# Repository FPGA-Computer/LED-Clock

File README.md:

This is an accurate 6 digitals clock (HH.MM.SS) for the STM8S003.

Details: https://hw-by-design.blogspot.com/2019/11/stm8-led-clock-part-1.html

The RTC is implemented in firmware. It uses a 24-bit numerically-controlled 
oscillator (NCO) in formware for very fine accuracy adjustment.

Mine has been calibrated to within +/- 1 sec/month 
(room temperature is regulated by heaters.)

Common cathode/ 

efficient new 7 seg display with common cathode ~20mA

Common anode display/ 

old Alarm clock with recycled vintage large display from cable converter + 2 small displays. ~50mA
PNP anode drivers is needed.  Smaller display is more efficient, so I adjust their duty cycle in firmware.

Under those 2 directories:

Hardware/ - Eagle CAD schematic, PCB

Firmware/ - STM8S003 firmware source code

Firmware written by me are licensed under GPL 3.0.
It can be compiled using the free STM8 Cosmic C compiler.
Additional incorporated code are under their own licenses.

Hardware is licensed under CC BY-4.0

https://creativecommons.org/licenses/by/4.0/

History:

Initial release:
- bare minimal functionality, clock trim value is hard coded.

0.1 release
- added calendar

0.2 release
- added North America Daylight Saving Time (DST) + code clean up

0.3 release
- code cleanup
- added AC alarm clock using common anode display. Sorry messy wiring only, so no PCB

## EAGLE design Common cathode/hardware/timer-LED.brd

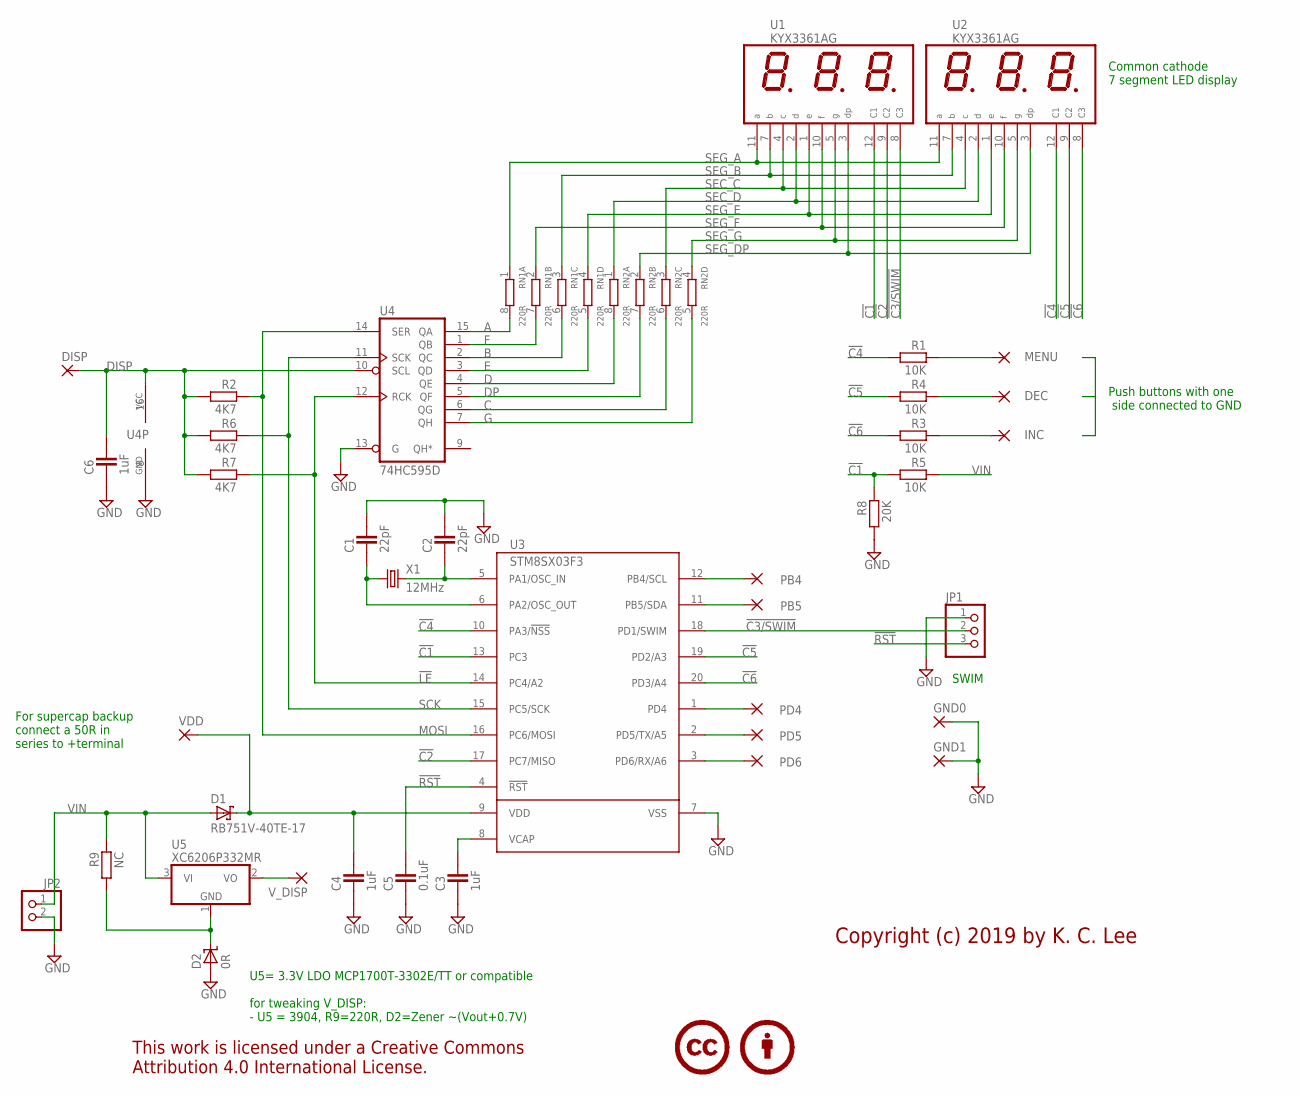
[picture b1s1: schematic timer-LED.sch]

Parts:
C1, C2: 22pF; CAPC1608X92N
C3, C4: 1uF; CAPC1608X92N
C5: 0.1uF; CAPC1608X92N
C6: 1uF; CAP2012X70N
D1: RB751V-40TE-17; SOD2514X100N
D2: 0R; SOD2514X100N
DEC: SMD2; SMD1,27-2,54
DISP: SMD2; SMD1,27-2,54
GND0, GND1: SMD2; SMD1,27-2,54
INC: SMD2; SMD1,27-2,54
JP1: PINHD-1X3; 1X03
JP2: PINHD-1X2_2.54; 1X02
LICENSE1: CC-BY75%; CC-BY-75
MENU: SMD2; SMD1,27-2,54
PB4, PB5: SMD2; SMD1,27-2,54
PD4, PD5, PD6: SMD2; SMD1,27-2,54
R1, R5: 10K; RESC1608X55N
R2, R6, R7: 4K7; RESC1608X55N
R3, R4: 10K; RESC2012X70N
R8: 20K; RESC1608X55N
R9: NC; RESC1608X55N
RN1, RN2: 220R; CAT16
U1, U2: KYX3361AG; KYX3361
U3: STM8SX03F3; TSSOP20
U4: 74HC595D; SO16
U5: XC6206P332MR; SOT95P280X135-3N
VDD: SMD2; SMD1,27-2,54
V_DISP: SMD2; SMD1,27-2,54
X1: 12MHz; HC49U-V

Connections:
!C1: R5.2, R8.1, U1.12 (C1), U3.13 (PC3)
!C2: U1.9 (C2), U3.17 (PC7/MISO)
!C3/SWIM: JP1.2, U1.8 (C3), U3.18 (PD1/SWIM)
!C4: R1.2, U2.12 (C1), U3.10 (PA3/!NSS)
!C5: R4.2, U2.9 (C2), U3.19 (PD2/A3)
!C6: R3.2, U2.8 (C3), U3.20 (PD3/A4)
!LE: R7.1, U3.14 (PC4/A2), U4.12 (RCK)
!RST: C5.2, JP1.3, U3.4 (!RST)
A: RN1.8 (2), U4.15 (QA)
B: RN1.6 (2), U4.2 (QC)
C: RN2.6 (2), U4.6 (QG)
D: RN2.8 (2), U4.4 (QE)
DISP: C6.2, DISP.1, R2.2, R6.2, R7.2, U4.10 (SCL), U4.16 (VCC)
DP: RN2.7 (2), U4.5 (QF)
E: RN1.5 (2), U4.3 (QD)
F: RN1.7 (2), U4.1 (QB)
G: RN2.5 (2), U4.7 (QH)
GND: C1.2, C2.2, C3.1, C4.1, C5.1, C6.1, D2.A, GND0.1, GND1.1, JP1.1, JP2.2, R8.2, U3.7 (VSS), U4.8 (GND), U4.13 (G)
MOSI: R2.1, U3.16 (PC6/MOSI), U4.14 (SER)
unnamed: DEC.1, R4.1
unnamed: PB4.1, U3.12 (PB4/SCL)
unnamed: PB5.1, U3.11 (PB5/SDA)
unnamed: PD5.1, U3.2 (PD5/TX/A5)
unnamed: PD6.1, U3.3 (PD6/RX/A6)
unnamed: PD4.1, U3.1 (PD4)
unnamed: INC.1, R3.1
unnamed: U5.2 (VO), V_DISP.1
unnamed: C1.1, U3.6 (PA2/OSC_OUT), X1.1
unnamed: D2.K, R9.2, U5.1 (GND)
unnamed: C2.1, U3.5 (PA1/OSC_IN), X1.2
unnamed: C3.2, U3.8 (VCAP)
unnamed: MENU.1, R1.1
SCK: R6.1, U3.15 (PC5/SCK), U4.11 (SCK)
SEC_C: RN2.3 (1), U1.4 (C), U2.4 (C)
SEC_D: RN2.1, U1.2 (D), U2.2 (D)
SEG_A: RN1.1, U1.11 (A), U2.11 (A)
SEG_B: RN1.3 (1), U1.7 (B), U2.7 (B)
SEG_DP: RN2.2 (1), U1.3 (DP), U2.3 (DP)
SEG_E: RN1.4 (1), U1.1 (E), U2.1 (E)
SEG_F: RN1.2 (1), U1.10 (F), U2.10 (F)
SEG_G: RN2.4 (1), U1.5 (G), U2.5 (G)
VDD: C4.2, D1.K, U3.9 (VDD), VDD.1
VIN: D1.A, JP2.1, R5.1, R9.1, U5.3 (VI)

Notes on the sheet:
SWIM
U5= 3.3V LDO MCP1700T-3302E/TT or compatible for tweaking V_DISP: - U5 = 3904, R9=220R, D2=Zener ~(Vout+0.7V)
Copyright (c) 2019 by K. C. Lee
Push buttons with one side connected to GND
For supercap backup connect a 50R in series to +terminal
Common cathode 7 segment LED display

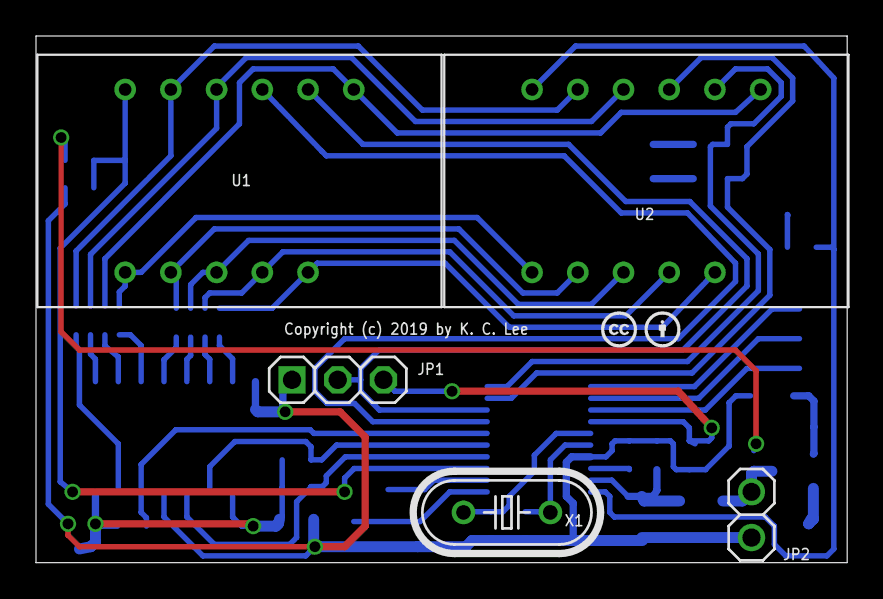
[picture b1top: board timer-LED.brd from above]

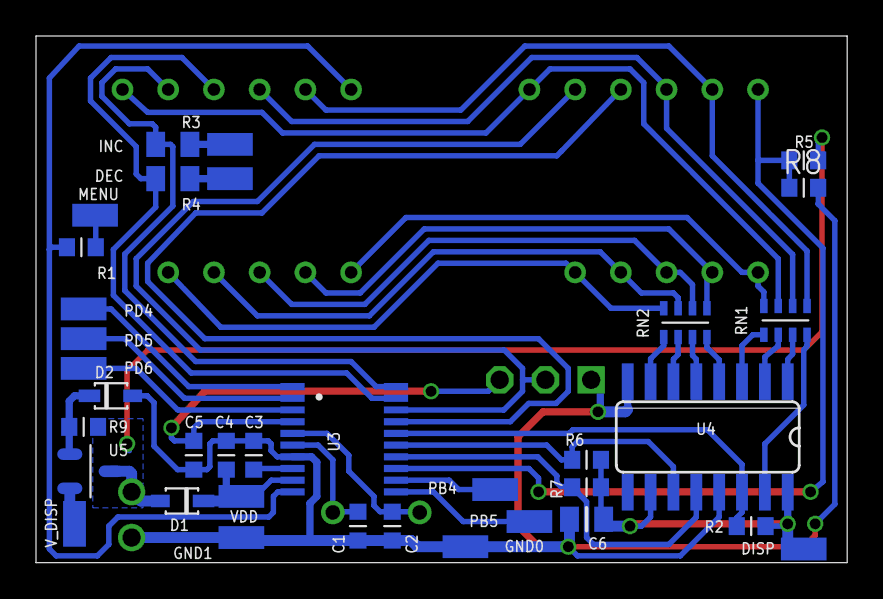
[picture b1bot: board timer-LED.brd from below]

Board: 2 copper layers, 45.1 x 29.3 mm, 41 parts (35 on the bottom side), 43 nets.

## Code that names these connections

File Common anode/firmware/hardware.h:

/*
 * hardware.h
 *
 * Created: October 31, 2019, 12:33:01 PM
 *  Author: K. C. Lee
 * Copyright (c) 2019 by K. C. Lee
 
 This program is free software: you can redistribute it and/or modify
 it under the terms of the GNU General Public License as published by
 the Free Software Foundation, either version 3 of the License, or
 (at your option) any later version.

 This program is distributed in the hope that it will be useful,
 but WITHOUT ANY WARRANTY; without even the implied warranty of
 MERCHANTABILITY or FITNESS FOR A PARTICULAR PURPOSE.  See the
 GNU General Public License for more details.

 You should have received a copy of the GNU General Public License
 along with this program.

 If not, see http://www.gnu.org/licenses/gpl-3.0.en.html 
 */ 

#ifndef HARDWARE_H_
#define HARDWARE_H_

#ifndef __CSMC__
#define __CSMC__
#endif
#define STM8S003

#include "stm8s.h"
#include <stdio.h>

// STM8S003F3P6
enum _PA { PA1=0x02, PA2=0x04, PA3=0x08 };
enum _PB { PB4=0x10, PB5=0x20 };
enum _PC { PC3=0x08, PC4=0x10, PC5=0x20, PC6=0x40, PC7=0x80 };
enum _PD { PD1=0x02, PD2=0x04, PD3=0x08, PD4=0x10, PD5=0x20, PD6=0x40 };

enum _7SEG_ENCODE
{
	SEG_A=0x01,SEG_F=0x02,SEG_B=0x04,SEG_E=0x08,
	SEG_D=0x10,SEG_DP=0x20,SEG_C=0x40,SEG_G=0x80
};

#define AC_CLOCK
#define _7SEG_ACTIVE_LOW	1

enum _CA_DRV
{ 
	CC1=PD2,CC1_PORT=GPIOD_BaseAddress,
	CC2=PD1,CC2_PORT=GPIOD_BaseAddress,
	CC3=PC7,CC3_PORT=GPIOC_BaseAddress,
	CC4=PC3,CC4_PORT=GPIOC_BaseAddress,
	CC5=PB4,CC5_PORT=GPIOB_BaseAddress,
	CC6=PB5,CC6_PORT=GPIOB_BaseAddress
};

#define SPI_SCK					PC5
#define SPI_MOSI				PC6
#define SPI_LE					PC4

#define SPI_PINS				(SPI_SCK|SPI_MOSI|SPI_LE)
#define SPI_PORT				GPIOC
		
// PD2/AIN3 is also used for key input
#define ADC_KEY_CH			(3)
#define ADC_KEY_PIN			PD2

#define PB_COLS					(CC5|CC6)
#define PC_COLS					(CC3|CC4)
#define PD_COLS					(CC1)							// non-SWIM
#define PD_SWIM					PD1

#define KEY_PC					(CC3|CC4|SPI_MOSI|SPI_LE)
#define KEY_PD					(CC1)

#define KEY_PC_SHIFT		3

enum keys_encoding 	{ B_ALARM=0x04,B_TIME=0x00,B_MIN=0x10,B_HOUR=0x01,B_SNOOZE=0x08,KEY_SW=0x02,

											KEY_MENU=B_HOUR,KEY_DEC=B_MIN,KEY_INC=B_ALARM,KEY_ALARM_OFF = B_SNOOZE,
											KEY_MASK=0x1f,
											KEY_LONG=0x20, KEY_REPORTED=0x40, KEY_FLAG=0x80
										};

#define KEY_COL					1
#define SENSE_COL				1

// CPU divider = 1 -> 12MHz
//#define CPU_DIV					0

// CPU divider = 16 -> 750kHz
//#define CPU_DIV					0x04
// CPU divider = 4 -> 3MHz
#define CPU_DIV					0x02
// CPU divider = 128 -> 93.75kHz
#define CPU_SLOW				0x07

#define GPIO(X)					((GPIO_TypeDef *)(X))

#define SW_MENU					CC4
#define SW_INC					CC5
#define SW_DEC					CC6

#define UART_TX					PD5
#define UART_RX					PD6
#define UART_PORT				GPIOD

#define COLUMN_MAX			5

#define CPU_CLOCK				12000000UL
#define EE_Addr					0x4000

// 12MHz/128 -> 93750Hz
#define TIM4_PSCR				0x07
// 93750Hz/256 = 366Hz.  Full refresh = 366Hz/6 columns -> 61Hz
#define TIM4_ARR				0xff
// Dynamically adjusting duty cycle to eualize brighter smaller digits
#define TIM4_ARR_DIM		0x50
#define LED_DIM_COL			0x04
#define LED_NOM_COL			0x00

#define SCAN_PER_SEC		(CPU_CLOCK/(1<<TIM4_PSCR)/(1+TIM4_ARR)/(COLUMN_MAX+1))

#define BEEP_ON					(BEEP_CSR_BEEPEN|0x1e|0x40)
#define BEEP_OFF				BEEP_CSR_RESET_VALUE
#define BEEP_MASK				0x09

#define Beep_On()				BEEP->CSR =BEEP_ON
#define Beep_Off()			BEEP->CSR = BEEP_OFF

typedef struct 
{
	uint8_t		Bit;
	uint16_t	Port;
} Column_Drv_t;

#include "irq.h"
#include "time.h"
#include "key.h"
#include "ui.h"
#include "clock.h"
#include "menu.h"
//#include "eeprom.h"
//#include "serial.h"

extern const Column_Drv_t ColumnDrv[];

extern volatile uint8_t Display_Col,tick,update,power,debugger;
extern volatile uint8_t Display[];
extern const uint8_t CharMap[];

void Init_Hardware(void);
void Update(void);
uint8_t Key_Scan(void);
void PowerDetect(void);

#endif

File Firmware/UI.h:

/*
 * UI.h
 *
 * Created: November 1, 2019, 6:22:57 PM
 *  Author: K. C. Lee
 * Copyright (c) 2019 by K. C. Lee
 
 This program is free software: you can redistribute it and/or modify
 it under the terms of the GNU General Public License as published by
 the Free Software Foundation, either version 3 of the License, or
 (at your option) any later version.

 This program is distributed in the hope that it will be useful,
 but WITHOUT ANY WARRANTY; without even the implied warranty of
 MERCHANTABILITY or FITNESS FOR A PARTICULAR PURPOSE.  See the
 GNU General Public License for more details.

 You should have received a copy of the GNU General Public License
 along with this program.

 If not, see http://www.gnu.org/licenses/gpl-3.0.en.html 
 */
 
#ifndef UI_H_
#define UI_H_

typedef struct
{	
	void	*Value;
	uint8_t	*Modified;
	uint8_t X;
	uint8_t Width;
	uint16_t Min;
	uint16_t Max;
	uint8_t Flags;
} UI_Item_t;

typedef struct
{	
	uint8_t		*Text;
	uint8_t		X;
	UI_Item_t *Items;
	uint8_t		Size;
} UI_Menu_t;

#define BLINK_EDIT_ITEM

typedef void (*FuncPtr)(void);
typedef void (*FuncPtr_arg)(void *);

#define UI_LARGE_STEP		10

enum DataFlags_ { D_HR, D_U8, D_U8Z, D_Str, D_SetExit
/*, D_Menu, D_Function, D_CustomData */ };

#define DISPLAY_MASK		0x1f
#define DISPLAY_ADJ			0x80

void sec2ms(uint16_t time,uint8_t *min,uint8_t *sec);

void UI_Print2d(int16_t Number,uint8_t Pos);
void UI_Print_Str(uint8_t *str,uint8_t x);
void UI_Fill(uint8_t ch, uint8_t x,uint8_t width);
void UI_Print_Hr(uint8_t hour,uint8_t display_opt);
void UI_Print_Time(rtc_t *time,uint8_t display_sec);
void UI_Print_Date(rtc_t *time);
void UI_PrintItems(UI_Menu_t *Menu);
uint8_t UI_Menu(UI_Menu_t *Menu);

#define ZERO_SUP				0x80
#define COL_MASK				0x0f

enum _Display_Options
{ 
	DISPLAY_SEC=0x01, DISPLAY_24H = 0x02
};

#define HR_COL					0
#define MIN_COL					2
#define SEC_COL					4

#define DOW_COL					0
#define DAY_COL					2
#define MONTH_COL				4

// UI limits year to 2 digits
#define CENTURY					2000

#define S_DAY_COL				0
#define S_MONTH_COL			2
#define S_YEAR_COL			4

//#define _AM_PM

#ifdef _AM_PM
	#define AM_SEG						SEG_F
	#define PM_SEG						SEG_E
#else
	#define AM_SEG						0
	#define PM_SEG						SEG_F
#endif

#define SEP_SEG							SEG_DP
#define CURSOR_SEG					SEG_D

/* 7 segment display

     --- A ---
    |         |
    F         B
    |         |
     --- G ---
    |         |
    E         C
    |         |
     --- D ---  DP
*/

enum _7Seg_chars
{
	Ch_0 =	SEG_A|SEG_B|SEG_C|SEG_D|SEG_E|SEG_F,
	Ch_1 =	      SEG_B|SEG_C,
	Ch_2 =	SEG_A|SEG_B|      SEG_D|SEG_E|      SEG_G,
	Ch_3 =	SEG_A|SEG_B|SEG_C|SEG_D|            SEG_G,
	Ch_4 =	      SEG_B|SEG_C|            SEG_F|SEG_G,
	Ch_5 =	SEG_A|      SEG_C|SEG_D|      SEG_F|SEG_G,
	Ch_6 =	SEG_A|      SEG_C|SEG_D|SEG_E|SEG_F|SEG_G,
	Ch_7 =	SEG_A|SEG_B|SEG_C,
	Ch_8 = SEG_A|SEG_B|SEG_C|SEG_D|SEG_E|SEG_F|SEG_G,
	Ch_9 =	SEG_A|SEG_B|SEG_C|SEG_D|      SEG_F|SEG_G,

	Ch_A = 	SEG_A|SEG_B|SEG_C|      SEG_E|SEG_F|SEG_G,
	Ch_B = 	            SEG_C|SEG_D|SEG_E|SEG_F|SEG_G,
	Ch_C = 	SEG_A|            SEG_D|SEG_E|SEG_F      ,
	Ch_D= 	      SEG_B|SEG_C|SEG_D|SEG_E|      SEG_G,
	Ch_E= 	SEG_A            |SEG_D|SEG_E|SEG_F|SEG_G,
	Ch_F = 	SEG_A                  |SEG_E|SEG_F|SEG_G,
	Ch_G = 	SEG_A|SEG_B|SEG_C|SEG_D      |SEG_F|SEG_G,
	Ch_H = 	      SEG_B|SEG_C      |SEG_E|SEG_F|SEG_G,
	Ch_I = 	                        SEG_E|SEG_F      ,
	Ch_J = 	      SEG_B|SEG_C|SEG_D|SEG_E            ,
	Ch_L = 	                  SEG_D|SEG_E|SEG_F      ,
	Ch_M1=	SEG_A|SEG_B            |SEG_E|SEG_F      ,
	Ch_M2= 	SEG_A|SEG_B|SEG_C            |SEG_F      ,
	Ch_N = 	SEG_A|SEG_B|SEG_C      |SEG_E|SEG_F      ,
	Ch_O = 	            SEG_C|SEG_D|SEG_E      |SEG_G,
	Ch_P = 	SEG_A|SEG_B            |SEG_E|SEG_F|SEG_G,	
	Ch_Q = 	SEG_A|SEG_B|SEG_C            |SEG_F|SEG_G,	
	Ch_R = 	                        SEG_E      |SEG_G,
	Ch_S = 	SEG_A      |SEG_C|SEG_D      |SEG_F|SEG_G,	
	Ch_T = 	                  SEG_D|SEG_E|SEG_F|SEG_G,
	Ch_U = 	      SEG_B|SEG_C|SEG_D|SEG_E|SEG_F      ,
	Ch_V = 	            SEG_C|SEG_D|SEG_E|SEG_F      ,
	Ch_W1= 	            SEG_C|SEG_D|SEG_E|SEG_F      ,
	Ch_W2= 	      SEG_B|SEG_C|SEG_D|SEG_E            ,
	Ch_Y = 	      SEG_B|SEG_C|SEG_D      |SEG_F|SEG_G,
	
	Ch_h = 	            SEG_C      |SEG_E|SEG_F|SEG_G,	
	Ch_r = 	                        SEG_E      |SEG_G,
	Ch_u = 	            SEG_C|SEG_D|SEG_E            ,	
	
	Ch_Neg = SEG_G
};

#ifdef HEX_PRINT
#define  HEX_CHAR
void PrintHex24(uint32_t N);
#endif

#endif

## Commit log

2020-01-12 initial release
2020-01-12 readme
2020-01-15 Add Calendar
2020-01-15 typo
2020-01-16 DST + cleanup
2020-01-26 fixed day of week bug in RTC
2020-02-05 Set DST states after time/date set
2020-11-01 fix daylight saving time
2020-12-03 bug fixes and maintances
2021-03-04 Add AC alarm clock
2021-03-04 fix readme
2021-03-09 fix DST start/end dates

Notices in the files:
parts and their libraries:
Misc logo: This work is licensed under a Creative Commons
Attribution 4.0 International License.
